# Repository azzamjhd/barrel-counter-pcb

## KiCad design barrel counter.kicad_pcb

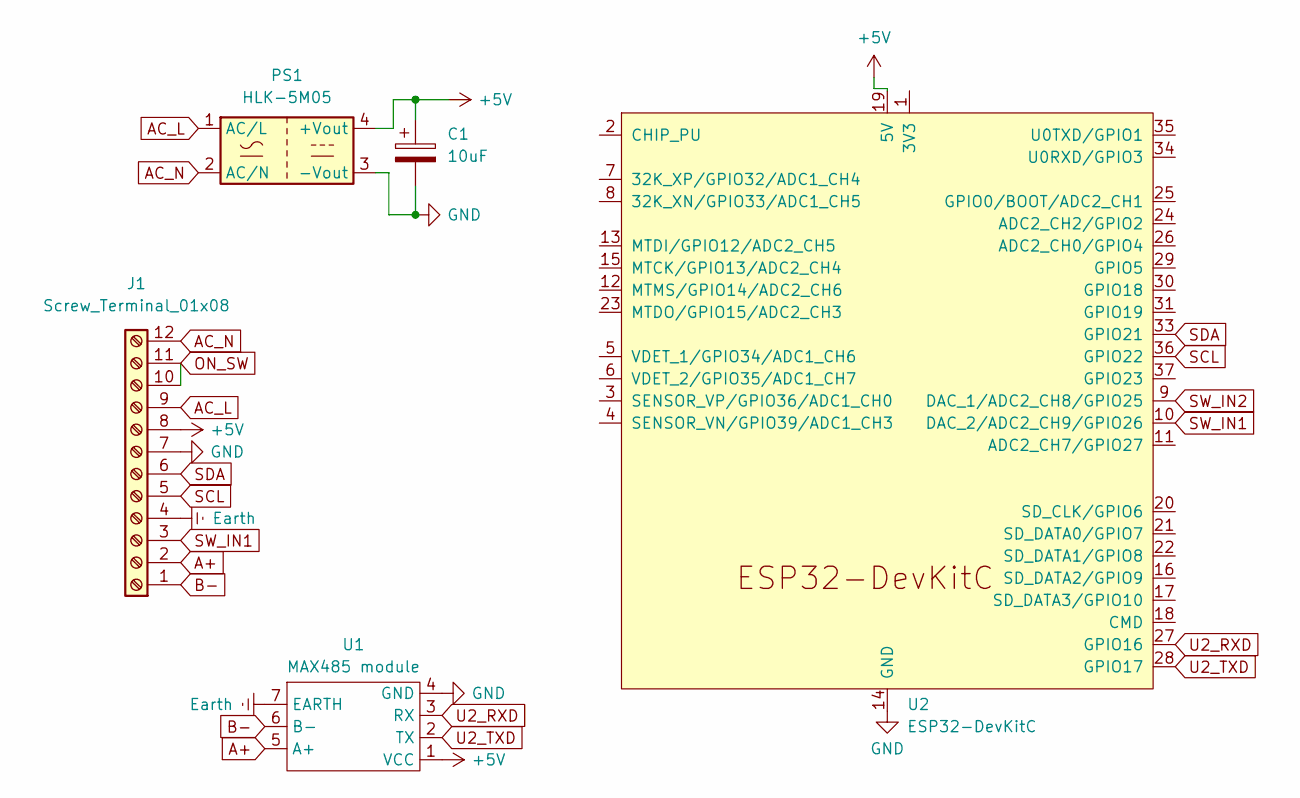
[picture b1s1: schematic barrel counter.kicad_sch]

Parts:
C1: 10uF; CP_Radial_D5.0mm_P2.50mm
J1: Screw_Terminal_01x08; PhoenixContact_MSTBA_2,5_12-G-5,08_1x12_P5.08mm_Horizontal
PS1: HLK-5M05; Converter_ACDC_Hi-Link_HLK-5Mxx
U1: MAX485 module; MAX485_MOD
U2: ESP32-DevKitC

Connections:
+5V: C1.1, J1.8, PS1.4 (+Vout), U1.1 (VCC), U2.19 (5V)
A+: J1.2, U1.5 (A+)
AC_L: J1.9, PS1.1 (AC/L)
AC_N: J1.12, PS1.2 (AC/N)
B-: J1.1, U1.6 (B-)
Earth: J1.4, U1.7 (EARTH)
GND: C1.2, J1.7, PS1.3 (-Vout), U1.4 (GND), U2.14 (GND), U2.32 (GND), U2.38 (GND)
ON_SW: J1.10, J1.11
SCL: J1.5, U2.36 (GPIO22)
SDA: J1.6, U2.33 (GPIO21)
SW_IN1: J1.3, U2.10 (DAC_2/ADC2_CH9/GPIO26)
SW_IN2: U2.9 (DAC_1/ADC2_CH8/GPIO25)
U2_RXD: U1.3 (RX), U2.27 (GPIO16)
U2_TXD: U1.2 (TX), U2.28 (GPIO17)

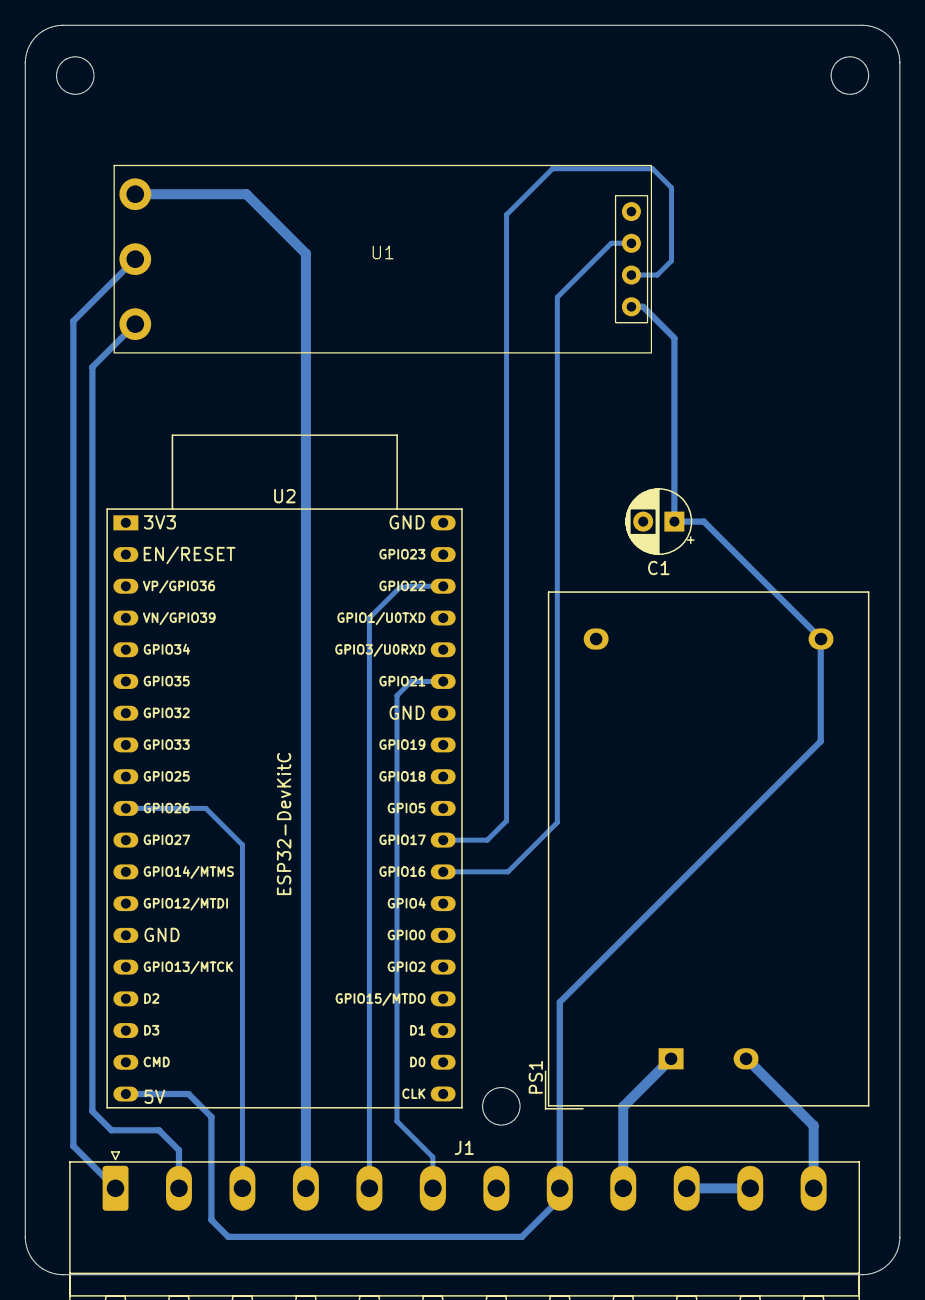
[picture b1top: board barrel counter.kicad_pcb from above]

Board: 2 copper layers, 70.0 x 100.0 mm, 5 parts (0 on the bottom side), 13 nets.

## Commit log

2025-03-06 added gitignore file
